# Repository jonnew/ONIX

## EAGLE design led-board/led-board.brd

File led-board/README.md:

# led-board
Simple board for making pig-tailed, drivable stimulation LEDs for optogenetic
manipulation.

## Gerber Files
{% include gerber_layers.md %}

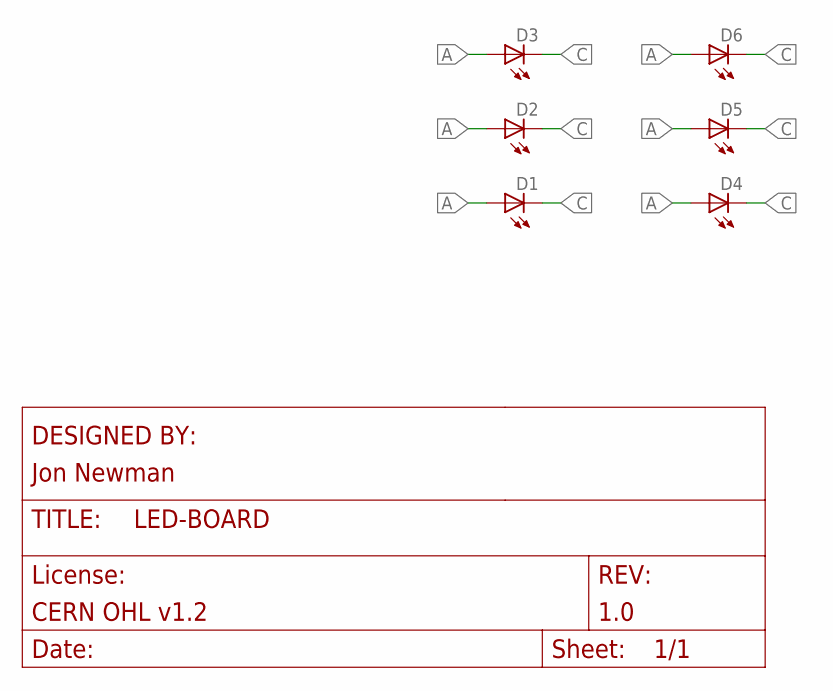
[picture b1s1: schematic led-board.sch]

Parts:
D1, D2, D3, D4, D5, D6: LED_LXZ1; LXZ1

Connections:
A: D1.A, D2.A, D3.A, D4.A, D5.A, D6.A
C: D1.C, D2.C, D3.C, D4.C, D5.C, D6.C

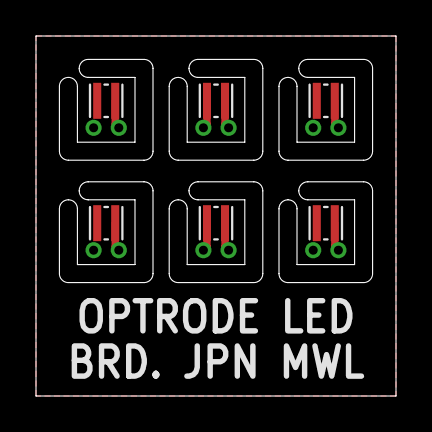
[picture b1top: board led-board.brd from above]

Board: 2 copper layers, 20.0 x 20.0 mm, 6 parts (0 on the bottom side), 2 nets.

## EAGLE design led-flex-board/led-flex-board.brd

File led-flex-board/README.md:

### led-flex-board
Simple flexible board for making pig-tailed, driveable stimulation LEDs for
optogenetic manipulation using standard chip scale LEDs or direct-attach micro
LEDs.

## Gerber Files
{% include gerber_layers.md %}

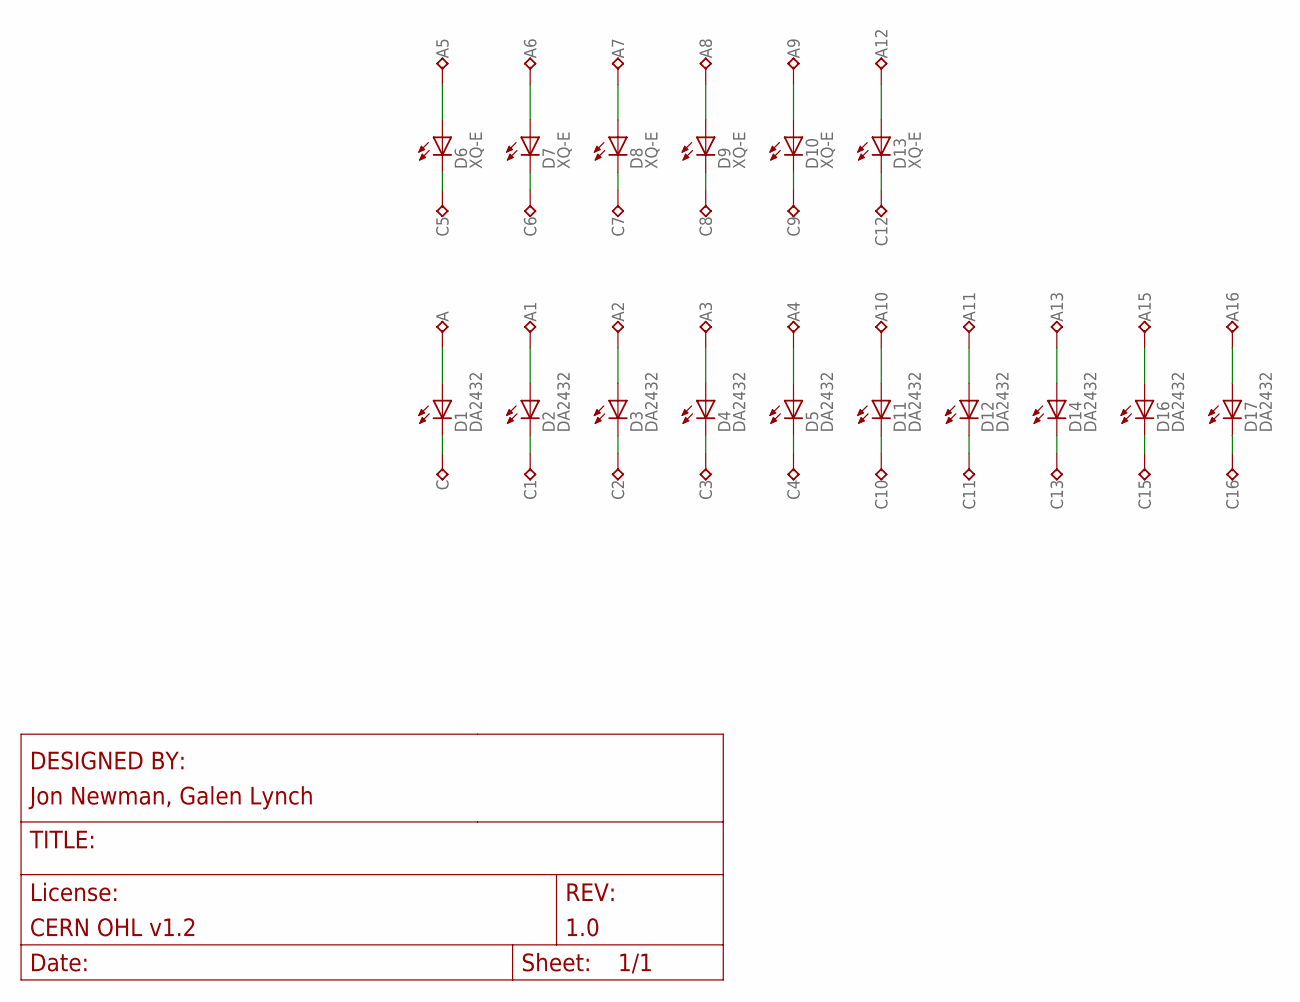
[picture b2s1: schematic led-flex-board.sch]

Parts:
A, A1, A2, A3, A4, A5, A6, A7, A8, A9, A10, A11, A12, A13, A15, A16: TP_S0.6X1.5MM; S0.6X1.5MM
C, C1, C2, C3, C4, C5, C6, C7, C8, C9, C10, C11, C12, C13, C15, C16: TP_S0.6X1.5MM; S0.6X1.5MM
D1, D2, D3, D4, D5, D11, D12, D14, D16, D17: DA2432
D6, D7, D8, D9, D10, D13: XQ-E; XLAMP_1.6X1.6MM

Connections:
unnamed: C.TP, D1.C
unnamed: A.TP, D1.A
unnamed: C1.TP, D2.C
unnamed: A1.TP, D2.A
unnamed: C2.TP, D3.C
unnamed: A2.TP, D3.A
unnamed: C3.TP, D4.C
unnamed: A3.TP, D4.A
unnamed: C4.TP, D5.C
unnamed: A4.TP, D5.A
unnamed: C5.TP, D6.C
unnamed: A5.TP, D6.A
unnamed: C6.TP, D7.C
unnamed: A6.TP, D7.A
unnamed: C7.TP, D8.C
unnamed: A7.TP, D8.A
unnamed: C8.TP, D9.C
unnamed: A8.TP, D9.A
unnamed: C9.TP, D10.C
unnamed: A9.TP, D10.A
unnamed: C10.TP, D11.C
unnamed: A10.TP, D11.A
unnamed: C11.TP, D12.C
unnamed: A11.TP, D12.A
unnamed: C12.TP, D13.C
unnamed: A12.TP, D13.A
unnamed: C13.TP, D14.C
unnamed: A13.TP, D14.A
unnamed: C15.TP, D16.C
unnamed: A15.TP, D16.A
unnamed: C16.TP, D17.C
unnamed: A16.TP, D17.A

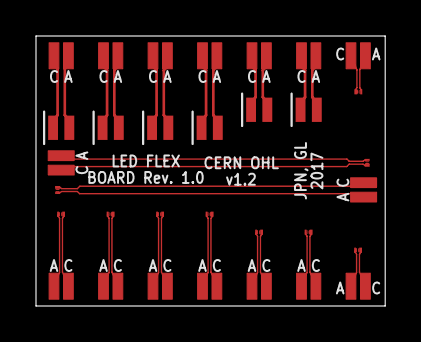
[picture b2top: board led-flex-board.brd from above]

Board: 1 copper layer, 19.4 x 15.0 mm, 48 parts (0 on the bottom side), 32 nets.

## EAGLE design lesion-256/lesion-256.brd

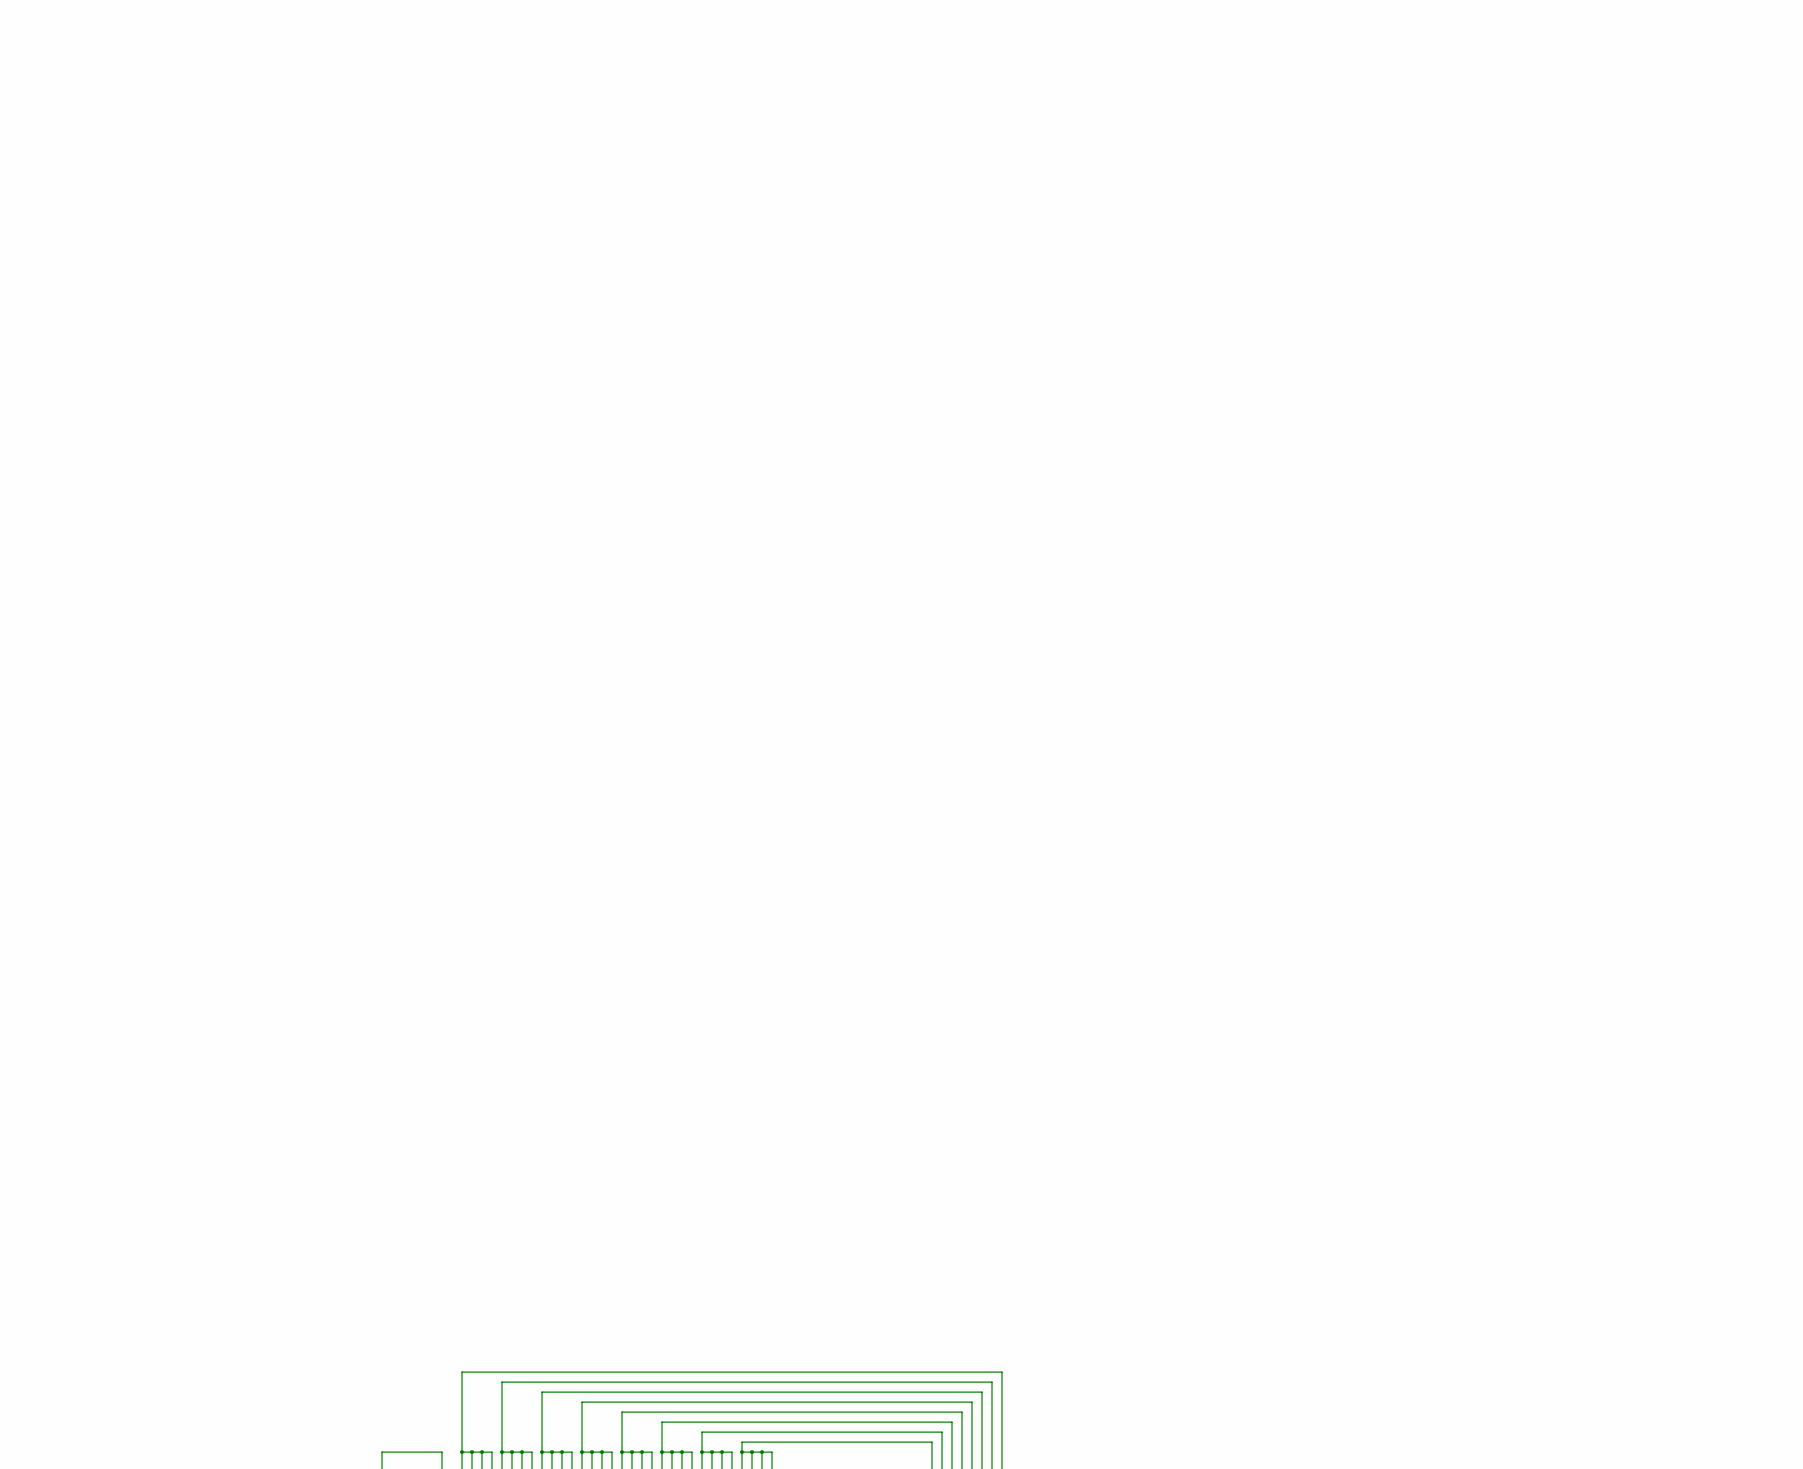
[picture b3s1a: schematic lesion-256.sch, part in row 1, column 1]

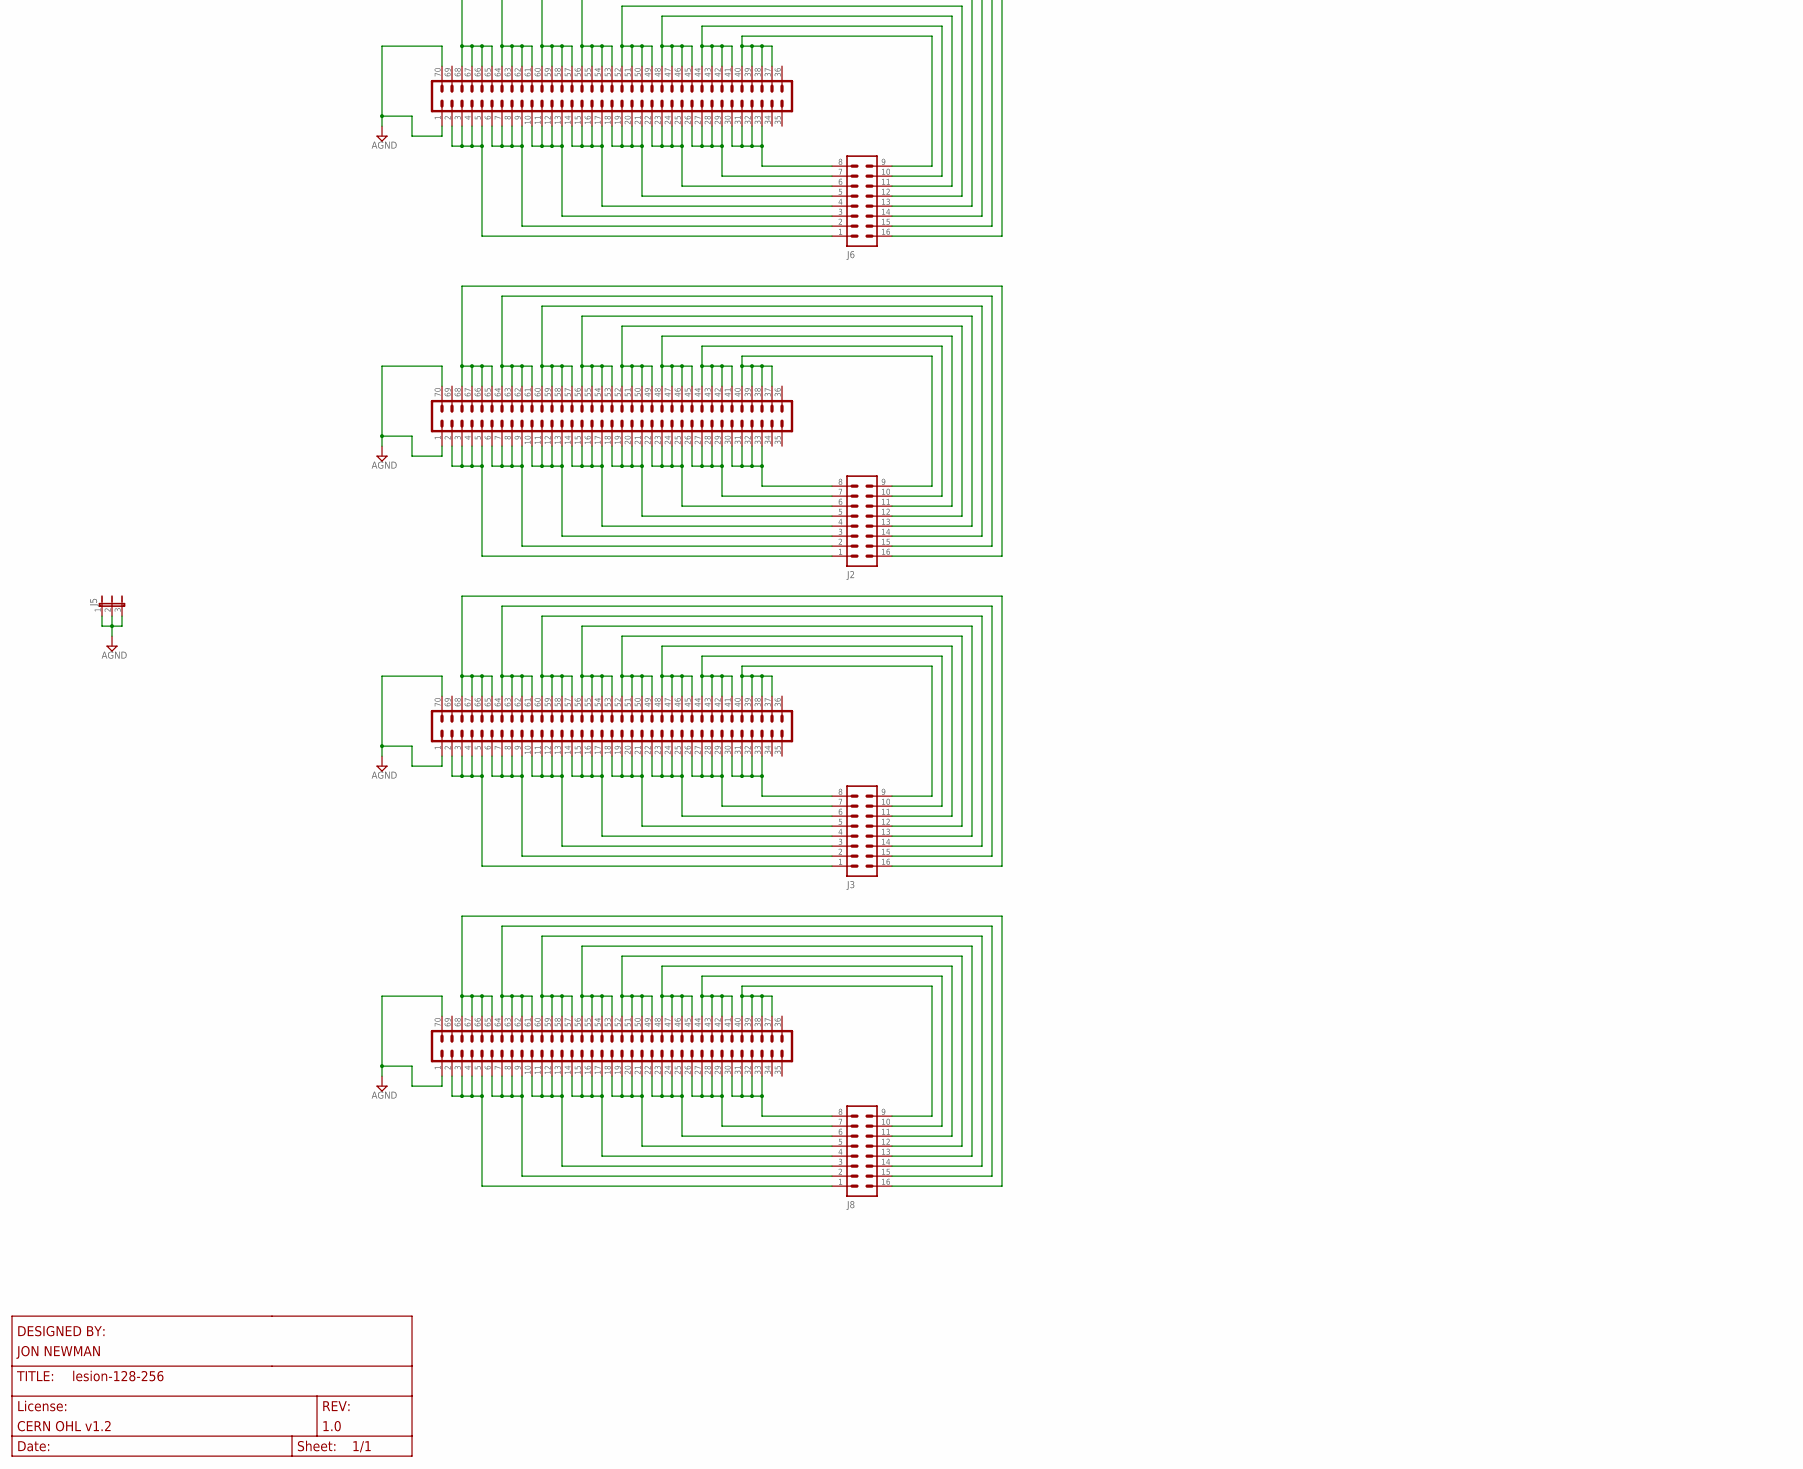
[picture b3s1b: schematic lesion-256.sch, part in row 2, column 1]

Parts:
J2, J3, J6, J8: PINHD-2X8_SMD_0.5"; JP2X8_SMD_0.5"
J5: JP3E_SMD-0.05; JP3_SMD-0.05
JA1, JA3, JA5, JA7: DF40C(2.0)-70DS-0.4V(51); DF40-70REC

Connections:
AGND: J5.1, J5.2, J5.3, JA1.1, JA1.70, JA3.1, JA3.70, JA5.1, JA5.70, JA7.1, JA7.70
unnamed: J2.1, JA1.2, JA1.3, JA1.4, JA1.5
unnamed: J2.2 (3), JA1.6, JA1.7, JA1.8, JA1.9
unnamed: J2.3 (5), JA1.10, JA1.11, JA1.12, JA1.13
unnamed: J2.4 (7), JA1.14, JA1.15, JA1.16, JA1.17
unnamed: J2.5 (9), JA1.18, JA1.19, JA1.20, JA1.21
unnamed: J2.6 (11), JA1.22, JA1.23, JA1.24, JA1.25
unnamed: J2.7 (13), JA1.26, JA1.27, JA1.28, JA1.29
unnamed: J2.8 (15), JA1.30, JA1.31, JA1.32, JA1.33
unnamed: J2.9 (16), JA1.37, JA1.38, JA1.39, JA1.40
unnamed: J2.10 (14), JA1.41, JA1.42, JA1.43, JA1.44
unnamed: J2.11 (12), JA1.45, JA1.46, JA1.47, JA1.48
unnamed: J2.12 (10), JA1.49, JA1.50, JA1.51, JA1.52
unnamed: J2.13 (8), JA1.53, JA1.54, JA1.55, JA1.56
unnamed: J2.14 (6), JA1.57, JA1.58, JA1.59, JA1.60
unnamed: J2.15 (4), JA1.61, JA1.62, JA1.63, JA1.64
unnamed: J2.16 (2), JA1.65, JA1.66, JA1.67, JA1.68
unnamed: J3.1, JA3.2, JA3.3, JA3.4, JA3.5
unnamed: J3.2 (3), JA3.6, JA3.7, JA3.8, JA3.9
unnamed: J3.3 (5), JA3.10, JA3.11, JA3.12, JA3.13
unnamed: J3.4 (7), JA3.14, JA3.15, JA3.16, JA3.17
unnamed: J3.5 (9), JA3.18, JA3.19, JA3.20, JA3.21
unnamed: J3.6 (11), JA3.22, JA3.23, JA3.24, JA3.25
unnamed: J3.7 (13), JA3.26, JA3.27, JA3.28, JA3.29
unnamed: J3.8 (15), JA3.30, JA3.31, JA3.32, JA3.33
unnamed: J3.9 (16), JA3.37, JA3.38, JA3.39, JA3.40
unnamed: J3.10 (14), JA3.41, JA3.42, JA3.43, JA3.44
unnamed: J3.11 (12), JA3.45, JA3.46, JA3.47, JA3.48
unnamed: J3.12 (10), JA3.49, JA3.50, JA3.51, JA3.52
unnamed: J3.13 (8), JA3.53, JA3.54, JA3.55, JA3.56
unnamed: J3.14 (6), JA3.57, JA3.58, JA3.59, JA3.60
unnamed: J3.15 (4), JA3.61, JA3.62, JA3.63, JA3.64
unnamed: J3.16 (2), JA3.65, JA3.66, JA3.67, JA3.68
unnamed: J6.1, JA5.2, JA5.3, JA5.4, JA5.5
unnamed: J6.2 (3), JA5.6, JA5.7, JA5.8, JA5.9
unnamed: J6.3 (5), JA5.10, JA5.11, JA5.12, JA5.13
unnamed: J6.4 (7), JA5.14, JA5.15, JA5.16, JA5.17
unnamed: J6.5 (9), JA5.18, JA5.19, JA5.20, JA5.21
unnamed: J6.6 (11), JA5.22, JA5.23, JA5.24, JA5.25
unnamed: J6.7 (13), JA5.26, JA5.27, JA5.28, JA5.29
unnamed: J6.8 (15), JA5.30, JA5.31, JA5.32, JA5.33
unnamed: J6.9 (16), JA5.37, JA5.38, JA5.39, JA5.40
unnamed: J6.10 (14), JA5.41, JA5.42, JA5.43, JA5.44
unnamed: J6.11 (12), JA5.45, JA5.46, JA5.47, JA5.48
unnamed: J6.12 (10), JA5.49, JA5.50, JA5.51, JA5.52
unnamed: J6.13 (8), JA5.53, JA5.54, JA5.55, JA5.56
unnamed: J6.14 (6), JA5.57, JA5.58, JA5.59, JA5.60
unnamed: J6.15 (4), JA5.61, JA5.62, JA5.63, JA5.64
unnamed: J6.16 (2), JA5.65, JA5.66, JA5.67, JA5.68
unnamed: J8.1, JA7.2, JA7.3, JA7.4, JA7.5
unnamed: J8.2 (3), JA7.6, JA7.7, JA7.8, JA7.9
unnamed: J8.3 (5), JA7.10, JA7.11, JA7.12, JA7.13
unnamed: J8.4 (7), JA7.14, JA7.15, JA7.16, JA7.17
unnamed: J8.5 (9), JA7.18, JA7.19, JA7.20, JA7.21
unnamed: J8.6 (11), JA7.22, JA7.23, JA7.24, JA7.25
unnamed: J8.7 (13), JA7.26, JA7.27, JA7.28, JA7.29
unnamed: J8.8 (15), JA7.30, JA7.31, JA7.32, JA7.33
unnamed: J8.9 (16), JA7.37, JA7.38, JA7.39, JA7.40
unnamed: J8.10 (14), JA7.41, JA7.42, JA7.43, JA7.44
unnamed: J8.11 (12), JA7.45, JA7.46, JA7.47, JA7.48
unnamed: J8.12 (10), JA7.49, JA7.50, JA7.51, JA7.52
unnamed: J8.13 (8), JA7.53, JA7.54, JA7.55, JA7.56
unnamed: J8.14 (6), JA7.57, JA7.58, JA7.59, JA7.60
unnamed: J8.15 (4), JA7.61, JA7.62, JA7.63, JA7.64
unnamed: J8.16 (2), JA7.65, JA7.66, JA7.67, JA7.68

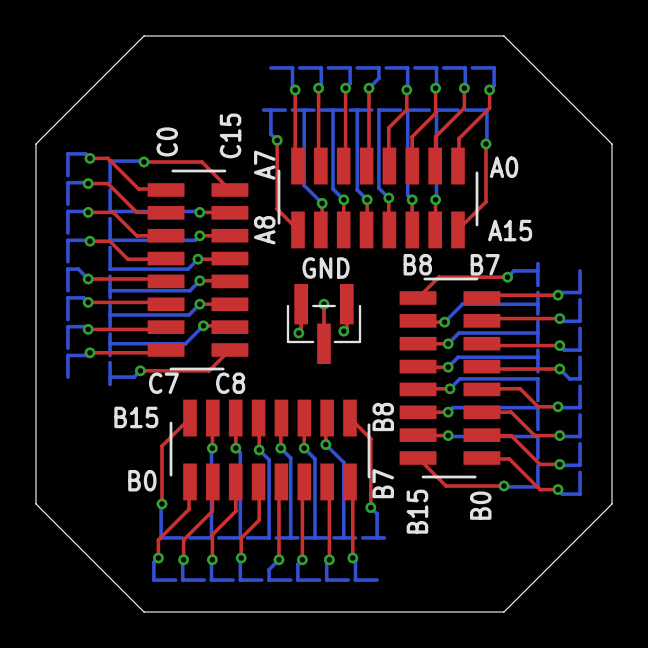
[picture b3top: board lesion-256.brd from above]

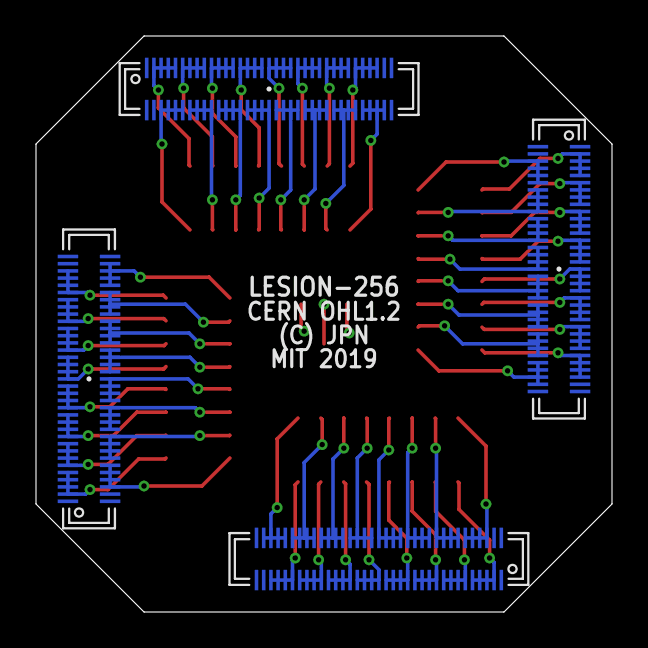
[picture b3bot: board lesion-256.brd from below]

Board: 2 copper layers, 32.0 x 32.0 mm, 9 parts (4 on the bottom side), 65 nets.

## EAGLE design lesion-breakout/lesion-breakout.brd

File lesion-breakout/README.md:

# Electro-lesioning breakout boards
These boards provide easy access to each tetrode on
[eib-64](../eib-64/README.md), [eib-128](../eib-128/README.md), and
[eib-256](../eib-256/README.md) for electro-lesioning or connectivity testing.

## Gerber Files
{% include gerber_layers.md %}

## Bill of Materials
The BOM is located on [this google
sheet](https://docs.google.com/spreadsheets/d/1F-KWcdvH_63iXjZf0cgCfDiFX6XXW3qw6rlR8DZrFpQ/edit#gid=1934583654).

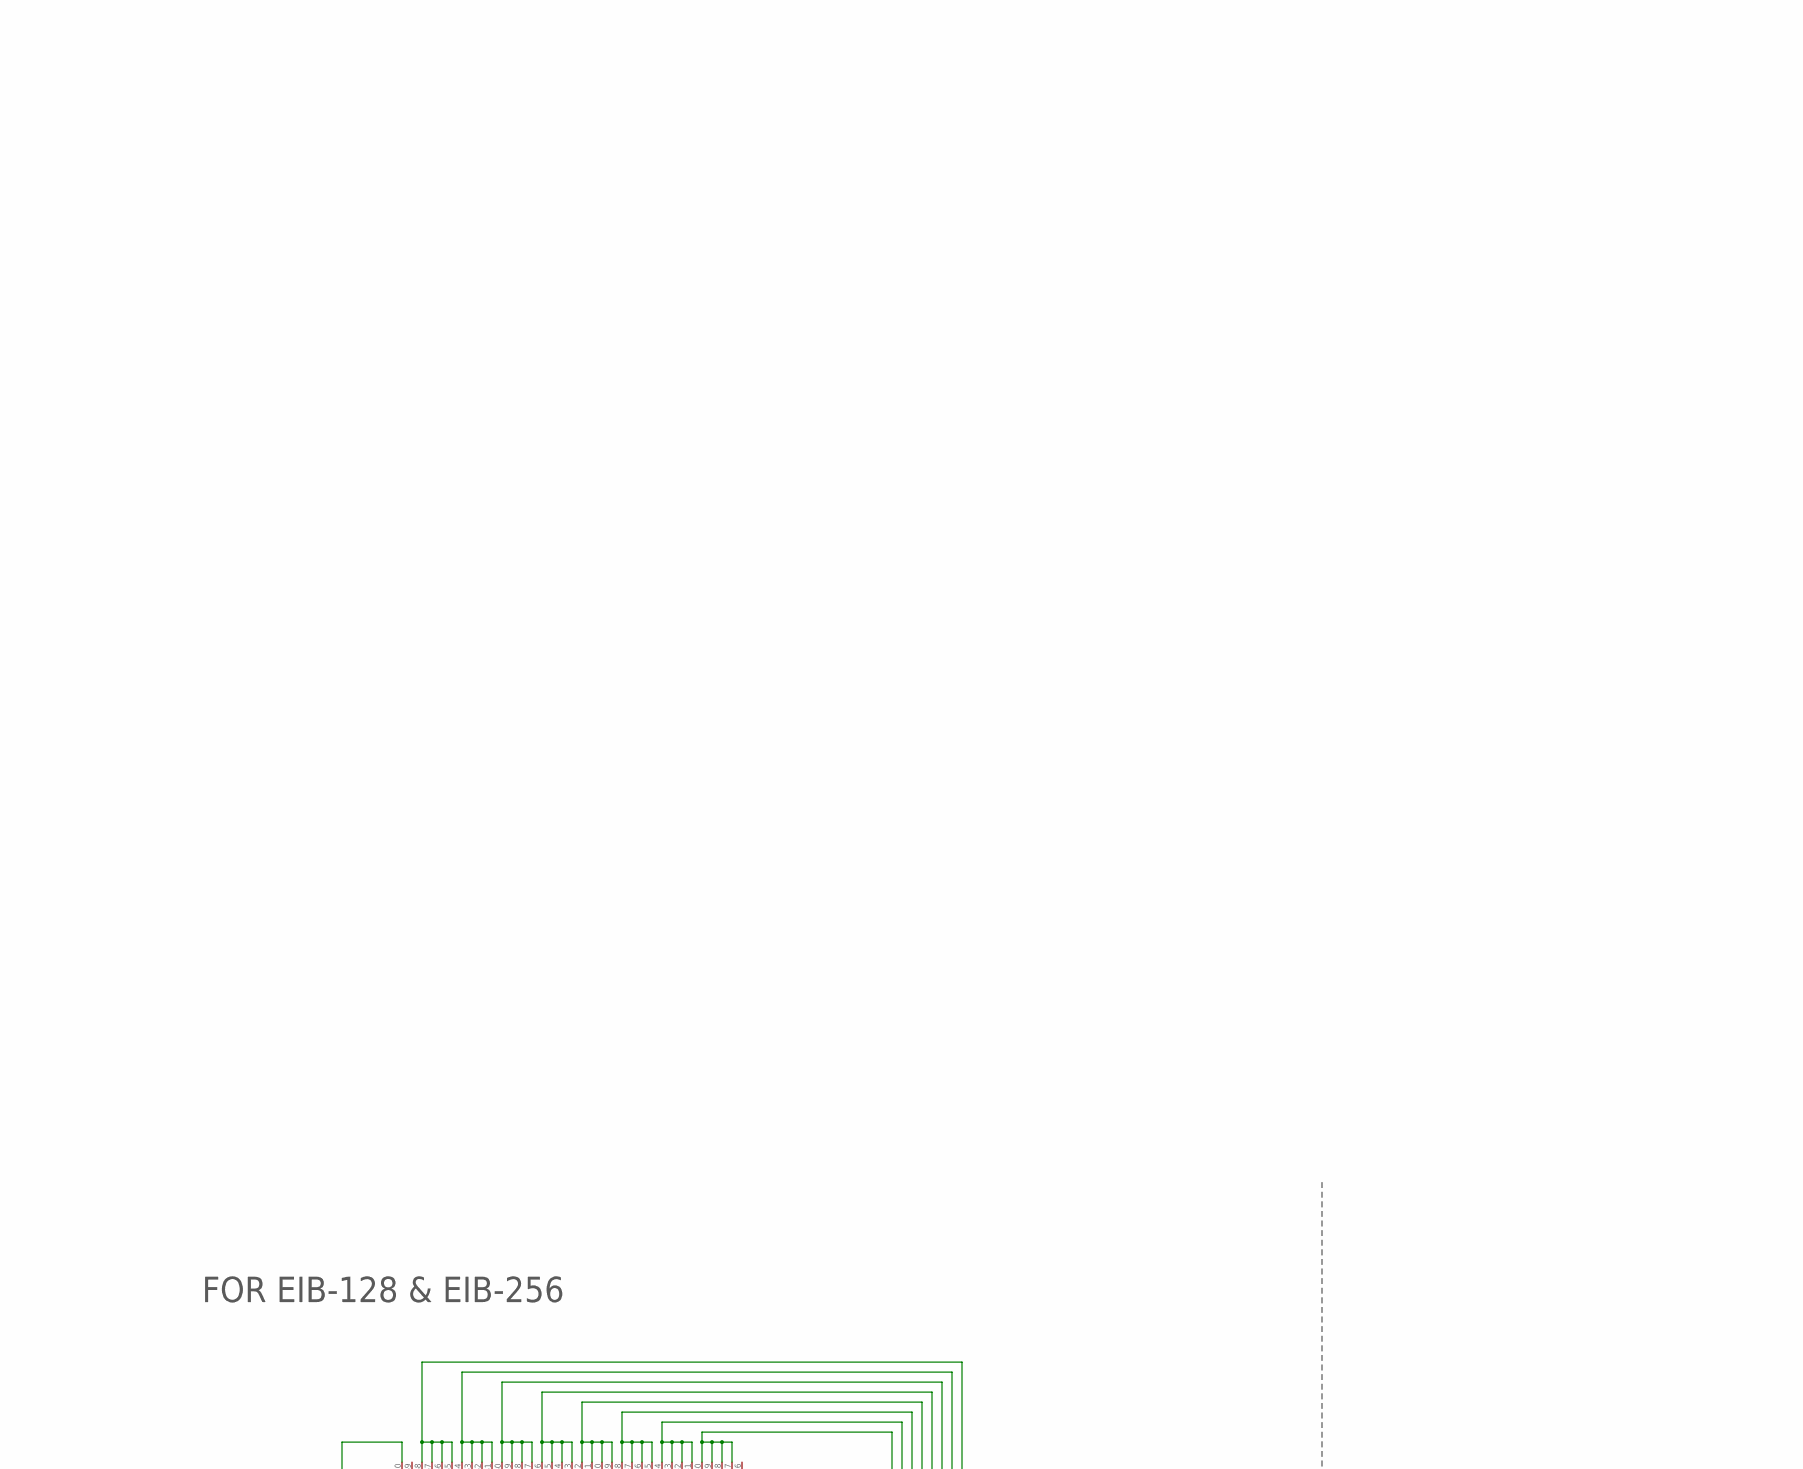
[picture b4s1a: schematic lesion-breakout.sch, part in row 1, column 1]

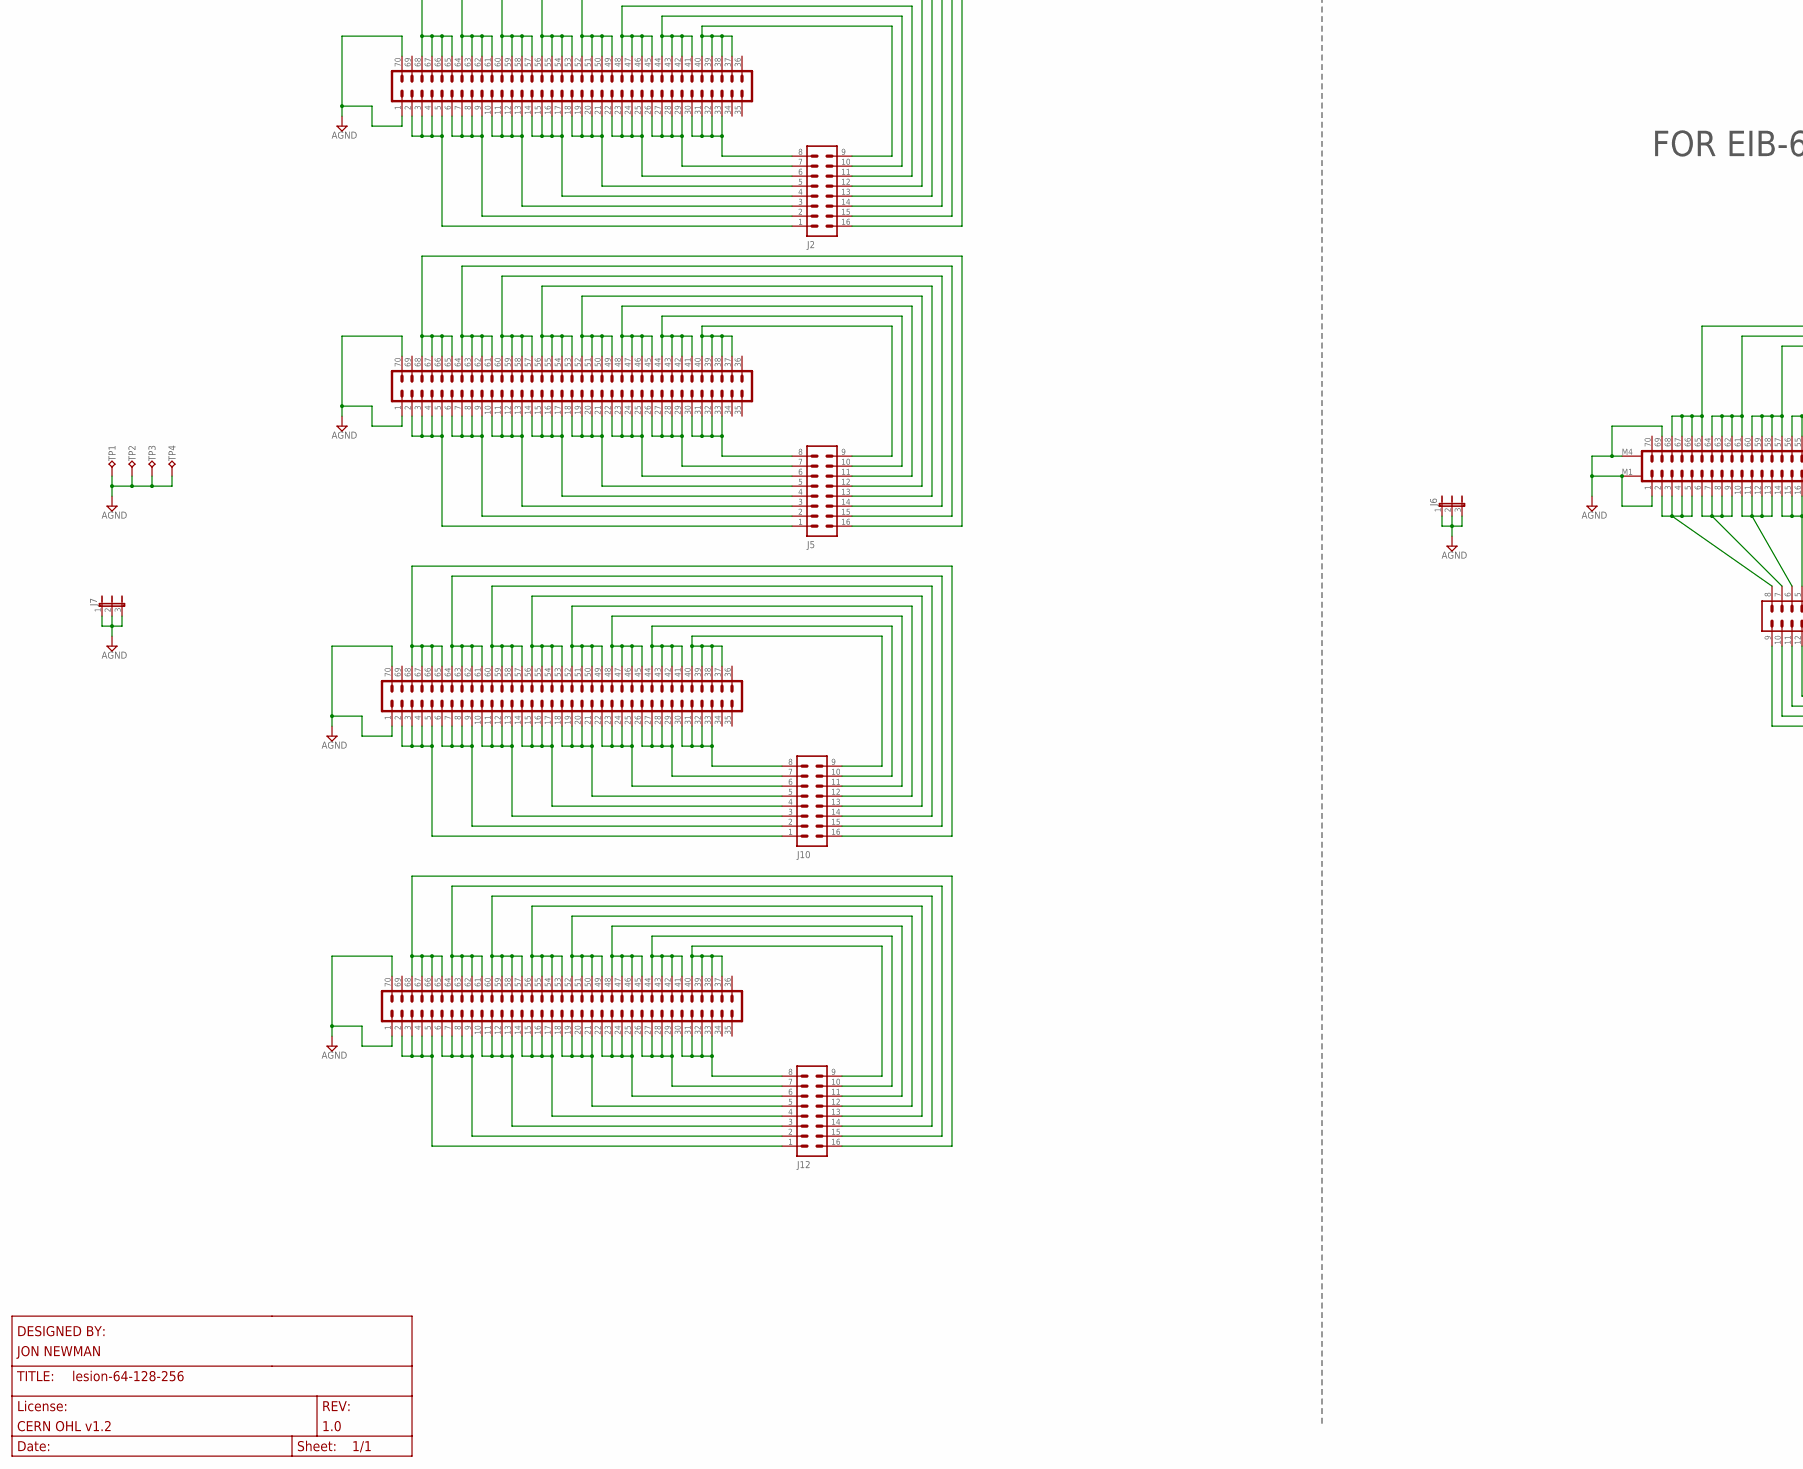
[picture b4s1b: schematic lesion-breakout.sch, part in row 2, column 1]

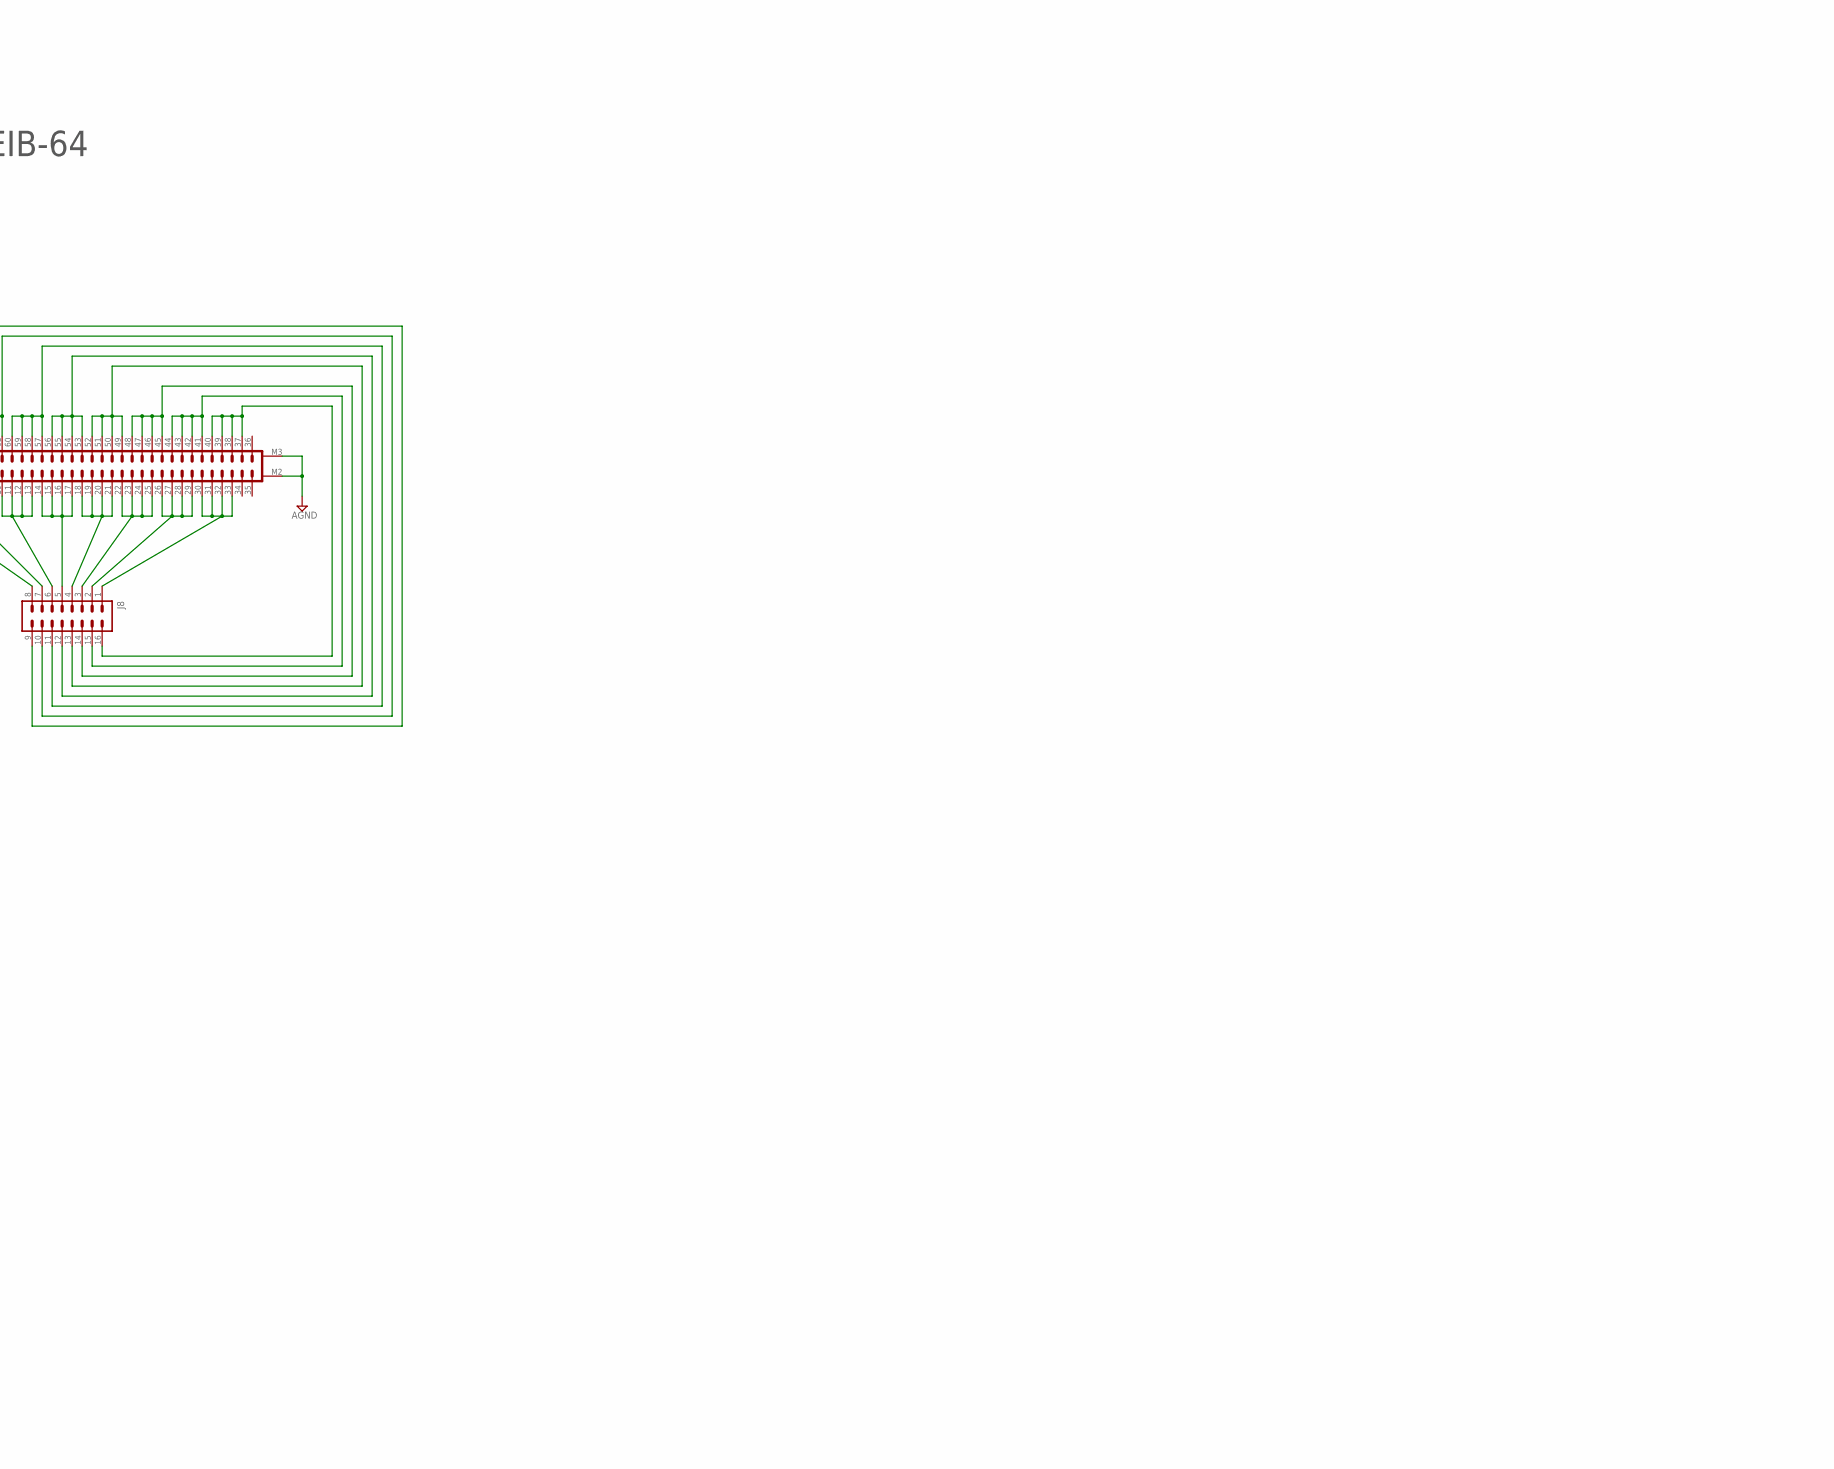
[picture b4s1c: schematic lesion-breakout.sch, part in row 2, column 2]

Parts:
J1, J3, J9, J11: DF40C(2.0)-70DS-0.4V(51); DF40-70REC
J2, J5, J8, J10, J12: PINHD-2X8_SMD_0.5"; JP2X8_SMD_0.5"
J4: DF40C-70DP-0.4V(51); DF40-70HEAD-LESS-SILK
J6, J7: JP3E_SMD-0.05; JP3_SMD-0.05
TP1, TP2, TP3, TP4: TP_1MM; TESTPOINT_1MM

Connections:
AGND: J1.1, J1.70, J3.1, J3.70, J4.1, J4.69, J4.M1, J4.M2, J4.M3, J4.M4, J6.1, J6.2, J6.3, J7.1, J7.2, J7.3, J9.1, J9.70, J11.1, J11.70, TP1.1, TP2.1, TP3.1, TP4.1
unnamed: J4.53, J4.54, J4.55, J4.56, J8.12 (10)
unnamed: J4.57, J4.58, J4.59, J4.60, J8.11 (12)
unnamed: J4.61, J4.62, J4.63, J4.64, J8.10 (14)
unnamed: J4.2, J4.3, J4.4, J4.5, J8.8 (15)
unnamed: J4.65, J4.66, J4.67, J4.68, J8.9 (16)
unnamed: J4.10, J4.11, J4.12, J4.13, J8.6 (11)
unnamed: J4.14, J4.15, J4.16, J4.17, J8.5 (9)
unnamed: J4.18, J4.19, J4.20, J4.21, J8.4 (7)
unnamed: J4.22, J4.23, J4.24, J4.25, J8.3 (5)
unnamed: J4.26, J4.27, J4.28, J4.29, J8.2 (3)
unnamed: J4.30, J4.31, J4.32, J4.33, J8.1
unnamed: J4.37, J4.38, J4.39, J4.40, J8.16 (2)
unnamed: J4.41, J4.42, J4.43, J4.44, J8.15 (4)
unnamed: J4.45, J4.46, J4.47, J4.48, J8.14 (6)
unnamed: J4.49, J4.50, J4.51, J4.52, J8.13 (8)
unnamed: J4.6, J4.7, J4.8, J4.9, J8.7 (13)
unnamed: J1.2, J1.3, J1.4, J1.5, J2.1
unnamed: J1.6, J1.7, J1.8, J1.9, J2.2 (3)
unnamed: J1.10, J1.11, J1.12, J1.13, J2.3 (5)
unnamed: J1.14, J1.15, J1.16, J1.17, J2.4 (7)
unnamed: J1.18, J1.19, J1.20, J1.21, J2.5 (9)
unnamed: J1.22, J1.23, J1.24, J1.25, J2.6 (11)
unnamed: J1.26, J1.27, J1.28, J1.29, J2.7 (13)
unnamed: J1.30, J1.31, J1.32, J1.33, J2.8 (15)
unnamed: J1.37, J1.38, J1.39, J1.40, J2.9 (16)
unnamed: J1.41, J1.42, J1.43, J1.44, J2.10 (14)
unnamed: J1.45, J1.46, J1.47, J1.48, J2.11 (12)
unnamed: J1.49, J1.50, J1.51, J1.52, J2.12 (10)
unnamed: J1.53, J1.54, J1.55, J1.56, J2.13 (8)
unnamed: J1.57, J1.58, J1.59, J1.60, J2.14 (6)
unnamed: J1.61, J1.62, J1.63, J1.64, J2.15 (4)
unnamed: J1.65, J1.66, J1.67, J1.68, J2.16 (2)
unnamed: J3.2, J3.3, J3.4, J3.5, J5.1
unnamed: J3.6, J3.7, J3.8, J3.9, J5.2 (3)
unnamed: J3.10, J3.11, J3.12, J3.13, J5.3 (5)
unnamed: J3.14, J3.15, J3.16, J3.17, J5.4 (7)
unnamed: J3.18, J3.19, J3.20, J3.21, J5.5 (9)
unnamed: J3.22, J3.23, J3.24, J3.25, J5.6 (11)
unnamed: J3.26, J3.27, J3.28, J3.29, J5.7 (13)
unnamed: J3.30, J3.31, J3.32, J3.33, J5.8 (15)
unnamed: J3.37, J3.38, J3.39, J3.40, J5.9 (16)
unnamed: J3.41, J3.42, J3.43, J3.44, J5.10 (14)
unnamed: J3.45, J3.46, J3.47, J3.48, J5.11 (12)
unnamed: J3.49, J3.50, J3.51, J3.52, J5.12 (10)
unnamed: J3.53, J3.54, J3.55, J3.56, J5.13 (8)
unnamed: J3.57, J3.58, J3.59, J3.60, J5.14 (6)
unnamed: J3.61, J3.62, J3.63, J3.64, J5.15 (4)
unnamed: J3.65, J3.66, J3.67, J3.68, J5.16 (2)
unnamed: J9.2, J9.3, J9.4, J9.5, J10.1
unnamed: J9.6, J9.7, J9.8, J9.9, J10.2 (3)
unnamed: J9.10, J9.11, J9.12, J9.13, J10.3 (5)
unnamed: J9.14, J9.15, J9.16, J9.17, J10.4 (7)
unnamed: J9.18, J9.19, J9.20, J9.21, J10.5 (9)
unnamed: J9.22, J9.23, J9.24, J9.25, J10.6 (11)
unnamed: J9.26, J9.27, J9.28, J9.29, J10.7 (13)
unnamed: J9.30, J9.31, J9.32, J9.33, J10.8 (15)
unnamed: J9.37, J9.38, J9.39, J9.40, J10.9 (16)
unnamed: J9.41, J9.42, J9.43, J9.44, J10.10 (14)
unnamed: J9.45, J9.46, J9.47, J9.48, J10.11 (12)
unnamed: J9.49, J9.50, J9.51, J9.52, J10.12 (10)
unnamed: J9.53, J9.54, J9.55, J9.56, J10.13 (8)
unnamed: J9.57, J9.58, J9.59, J9.60, J10.14 (6)
unnamed: J9.61, J9.62, J9.63, J9.64, J10.15 (4)
unnamed: J9.65, J9.66, J9.67, J9.68, J10.16 (2)
unnamed: J11.2, J11.3, J11.4, J11.5, J12.1
unnamed: J11.6, J11.7, J11.8, J11.9, J12.2 (3)
unnamed: J11.10, J11.11, J11.12, J11.13, J12.3 (5)
unnamed: J11.14, J11.15, J11.16, J11.17, J12.4 (7)
unnamed: J11.18, J11.19, J11.20, J11.21, J12.5 (9)
unnamed: J11.22, J11.23, J11.24, J11.25, J12.6 (11)
unnamed: J11.26, J11.27, J11.28, J11.29, J12.7 (13)
unnamed: J11.30, J11.31, J11.32, J11.33, J12.8 (15)
unnamed: J11.37, J11.38, J11.39, J11.40, J12.9 (16)
unnamed: J11.41, J11.42, J11.43, J11.44, J12.10 (14)
unnamed: J11.45, J11.46, J11.47, J11.48, J12.11 (12)
unnamed: J11.49, J11.50, J11.51, J11.52, J12.12 (10)
unnamed: J11.53, J11.54, J11.55, J11.56, J12.13 (8)
unnamed: J11.57, J11.58, J11.59, J11.60, J12.14 (6)
unnamed: J11.61, J11.62, J11.63, J11.64, J12.15 (4)
unnamed: J11.65, J11.66, J11.67, J11.68, J12.16 (2)

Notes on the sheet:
FOR EIB-128 & EIB-256
FOR EIB-64

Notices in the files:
led-board/led-board.sch:
LICENSE: CERN OHL v1.2
lesion-256/lesion-256.brd:
CERN OHL1.2
